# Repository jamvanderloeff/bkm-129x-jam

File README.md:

A full sized version of the BKM-129X compatible board, modified by jam

Rev. 1.0

BKM-129X-MCU code from https://github.com/skumlos/bkm-129x-mcu

Output ports are all actively buffered, so no need for terminators.

Connections from top to bottom when viewing component side, with BNCs to the left:
               _______________________________________
            __| _                                     |
Y/G IN     |___|_|                                    |
            __| _                                     |
Y/G OUT    |___|_|                                   _|
            __| _                                   | |
B-Y/B IN   |___|_|                                  | |
            __| _                                   | |
B-Y/B OUT  |___|_|                                  | |
            __| _                                   | |
R-Y/R IN   |___|_|                                  | |
            __| _                                   | |
R-Y/R OUT  |___|_|                                  | |
            __| _                                   |_|
SYNC IN    |___|_|                                    |
            __| _                                     |
SYNC OUT   |___|_|                                    |
              |_______________________________________|

Just like the original BKM-129X.

For more information go to https://immerhax.com/?p=422

You are welcome to clone, produce and sell hardware based on this. Please keep changes and so on open source.

Cool kids give credit where due.

Should be compatible with basically all monitors that accept the original BKM-129X

Check the MCU code for verified compatibility.

---------

Board revision history:

Jam's fork 1.0 

C: Fixed THS7374 filter bypass.

B: Added onboard MCU option

A: Initial version

---------

Copyright © 2020 Martin Hejnfelt <martin@hejnfelt.com> and 2021 James van der Loeff <jam@wakabavideo.com>
This work is free. You can redistribute it and/or modify it under the
terms of the Do What The Fuck You Want To Public License, Version 2,
as published by Sam Hocevar. See the LICENSE file for more details.

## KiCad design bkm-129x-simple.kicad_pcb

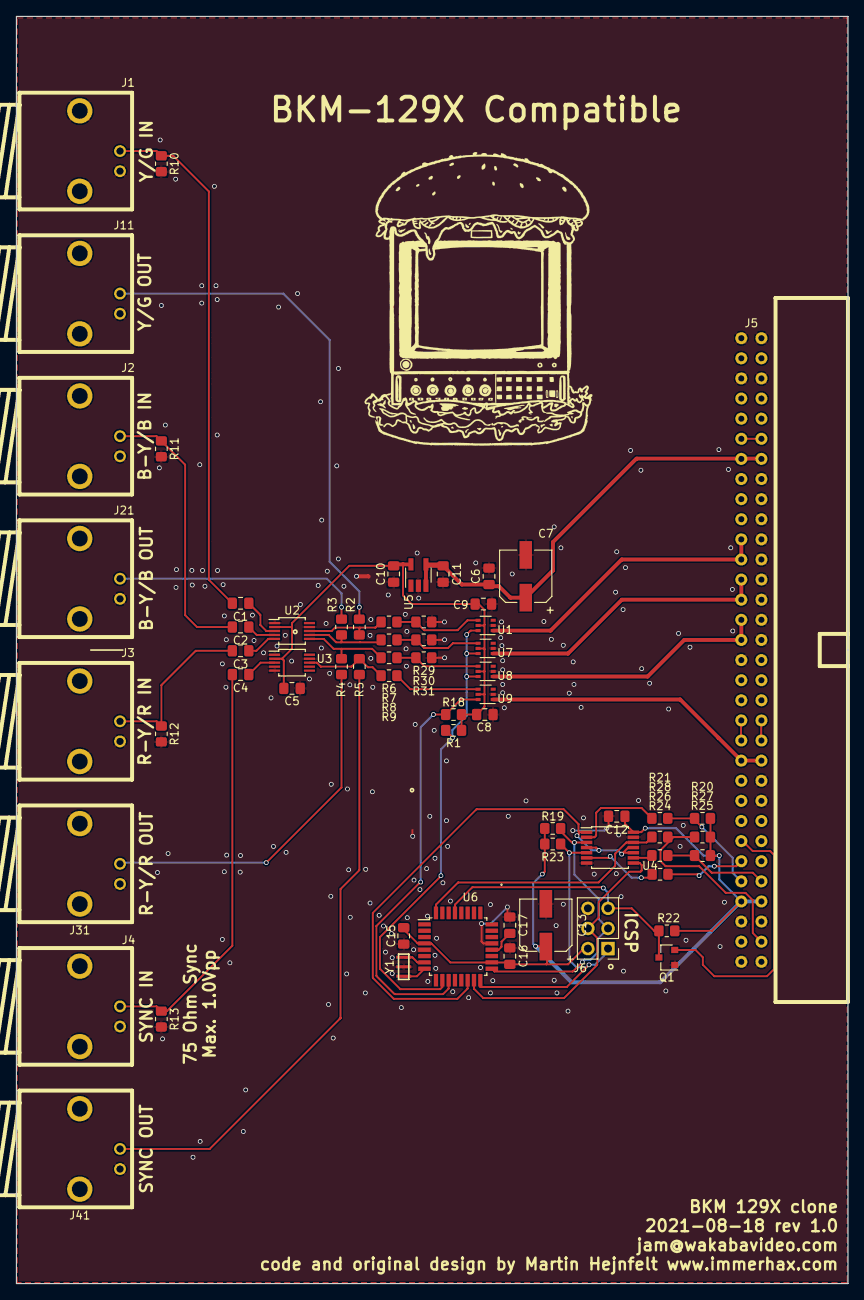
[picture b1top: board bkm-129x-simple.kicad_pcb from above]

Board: 2 copper layers, 105.0 x 160.0 mm, 65 parts (0 on the bottom side), 50 nets.

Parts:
C1, C2, C3, C4, C5, C6, C8, C9, C12, C17: 0.1uF; C_0805_2012Metric_Pad1.18x1.45mm_HandSolder
C7, C13: 100uF; CP_Elec_6.3x5.3
C10: 2.2uF; C_0805_2012Metric_Pad1.18x1.45mm_HandSolder
C11, C15: 1uF; C_0805_2012Metric_Pad1.18x1.45mm_HandSolder
C16: 4.7uF; C_0805_2012Metric_Pad1.18x1.45mm_HandSolder
FID1: Fiducial; borgar
J1: YG_IN; BNC-THT
J2: PBB_IN; BNC-THT
J3: PRR_IN; BNC-THT
J4: SYNC_IN; BNC-THT
J5: Conn_02x32_Row_Letter_Last; DIN-41612-64P
J6: ICSP; Pin_Header_Straight_2x03_Pitch2.54mm
J11: YG_OUT; BNC-THT
J21: PBB_OUT; BNC-THT
J31: PRR_OUT; BNC-THT
J41: SYNC_OUT; BNC-THT
Q1: DTC144EKAT146; SOT-23
R1, R18: 10K; R_0805_2012Metric_Pad1.20x1.40mm_HandSolder
R2, R3, R4, R5, R10, R11, R12, R13: 75R; R_0805_2012Metric_Pad1.20x1.40mm_HandSolder
R6, R7, R8, R29, R30, R31: 150R; R_0805_2012Metric_Pad1.20x1.40mm_HandSolder
R9: 0R; R_0805_2012Metric_Pad1.20x1.40mm_HandSolder
R19, R23: 4K7; R_0805_2012Metric_Pad1.20x1.40mm_HandSolder
R20, R22, R25, R27: 100K; R_0805_2012Metric_Pad1.20x1.40mm_HandSolder
R21, R24, R26, R28: 100R; R_0805_2012Metric_Pad1.20x1.40mm_HandSolder
U1, U7, U8, U9: BL1551; SOT-363_SC-70-6
U2, U3: TPF144-VR; MSOP-10_3x3mm_P0.5mm
U4: 74LVC125; TSSOP-14_4.4x5mm_Pitch0.65mm
U5: MIC3490-3.3; SOT-23-5_HandSoldering
U6: ATMEGA328PB-AU; TQFP-32_7x7mm_Pitch0.8mm
Y1: CSTNE16M0VH3L000R0; CSTNEx

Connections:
+3V3: C5.1, C8.1, C9.1, C10.1, R1.2, R18.1, U1.5, U2.2, U3.2, U5.5, U7.5, U8.5, U9.5
+5VD: C12.1, C13.1, C15.1, C16.1, J5.29a, J5.29b, J6.2, R19.2, R20.2, R22.1, R23.2, R25.2, R27.2, U4.14, U6.4, U6.18
/Bout: R3.1, R7.2, U2.7
/EXT_SYNC: J5.22a, J5.22b, U9.1
/MISO: J5.27b, R24.2
/MOSI: J5.28a, R25.1, R26.2
/P-B/B: J5.13b, J5.14b, U7.1
/P-R/R: J5.15b, J5.16b, U8.1
/RESET: J5.26b, Q1.2
/Rout: R4.1, R8.2, U2.6
/SCLK: J5.28b, R20.1, R21.2
/SLOT_ID: J5.31a, R27.1, R28.2
/Syncout: R5.1, R9.2, U3.8
/Y/G: J5.11b, J5.12b, U1.1
/Yout: R2.1, R6.2, U2.8
GND: C5.2, C6.2, C7.2, C8.2, C9.2, C10.2, C11.1, C12.2, C13.2, C15.2, C16.2, C17.1, J1.2, J2.2, J3.2, J4.2, J5.1a, J5.1b, J5.3a, J5.3b, J5.8a, J5.9a, J5.10a, J5.11a, J5.12a, J5.13a, J5.14a, J5.15a, J5.16a, J5.17b, J5.23a, J5.24a, J5.30a, J5.30b, J5.32a, J5.32b, J6.6, J11.2, J21.2, J31.2, J41.2, Q1.1, R10.2, R11.2, R12.2, R13.2, R29.2, R30.2, R31.2, U1.2, U2.1, U2.9, U3.1, U3.4, U3.5, U3.9, U4.7, U4.13, U5.2, U6.5, U6.21, U7.2, U8.2, U9.2, Y1.2
MCU_MISO: J6.1, R23.1, U4.5, U6.16
MCU_MOSI: J6.4, U4.8, U6.15
MCU_SCK: J6.3, R19.1, U4.3, U6.17
MCU_SLOT_ID: R28.1, U4.12, U6.32
unnamed: C1.1, U2.3
unnamed: C1.2, J1.1, R10.1
unnamed: C2.1, U2.4
unnamed: C2.2, J2.1, R11.1
unnamed: C3.1, U2.5
unnamed: C3.2, J3.1, R12.1
unnamed: C4.1, U3.3
unnamed: C4.2, J4.1, R13.1
unnamed: C17.2, U6.20
unnamed: J5.20a, J5.21a
unnamed: J5.20b, J5.21b
unnamed: J11.1, R2.2
unnamed: J21.1, R3.2
unnamed: J31.1, R4.2
unnamed: J41.1, R5.2
unnamed: R9.1, U9.4
unnamed: R21.1, U4.2
unnamed: R24.1, U4.6
unnamed: R26.1, U4.9
unnamed: R6.1, R29.1, U1.4
unnamed: R7.1, R30.1, U7.4
unnamed: R8.1, R31.1, U8.4
unnamed: U6.7, Y1.1
unnamed: U6.8, Y1.3
VDDA: C6.1, C7.1, C11.2, J5.7a, J5.7b, U5.3, U5.4
VSSA: J5.6a, J5.6b
~BX_OE: R1.1, U1.6, U6.10, U7.6, U8.6
~EXT_SYNC_OE: R18.2, U6.11, U9.6
~MCU_RESET: J6.5, Q1.3, R22.2, U6.29
~MCU_SS: U4.1, U4.4, U4.10, U4.11, U6.14

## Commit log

2021-08-18 redrawn, thanks skum
2021-08-18 first edit of the readme
